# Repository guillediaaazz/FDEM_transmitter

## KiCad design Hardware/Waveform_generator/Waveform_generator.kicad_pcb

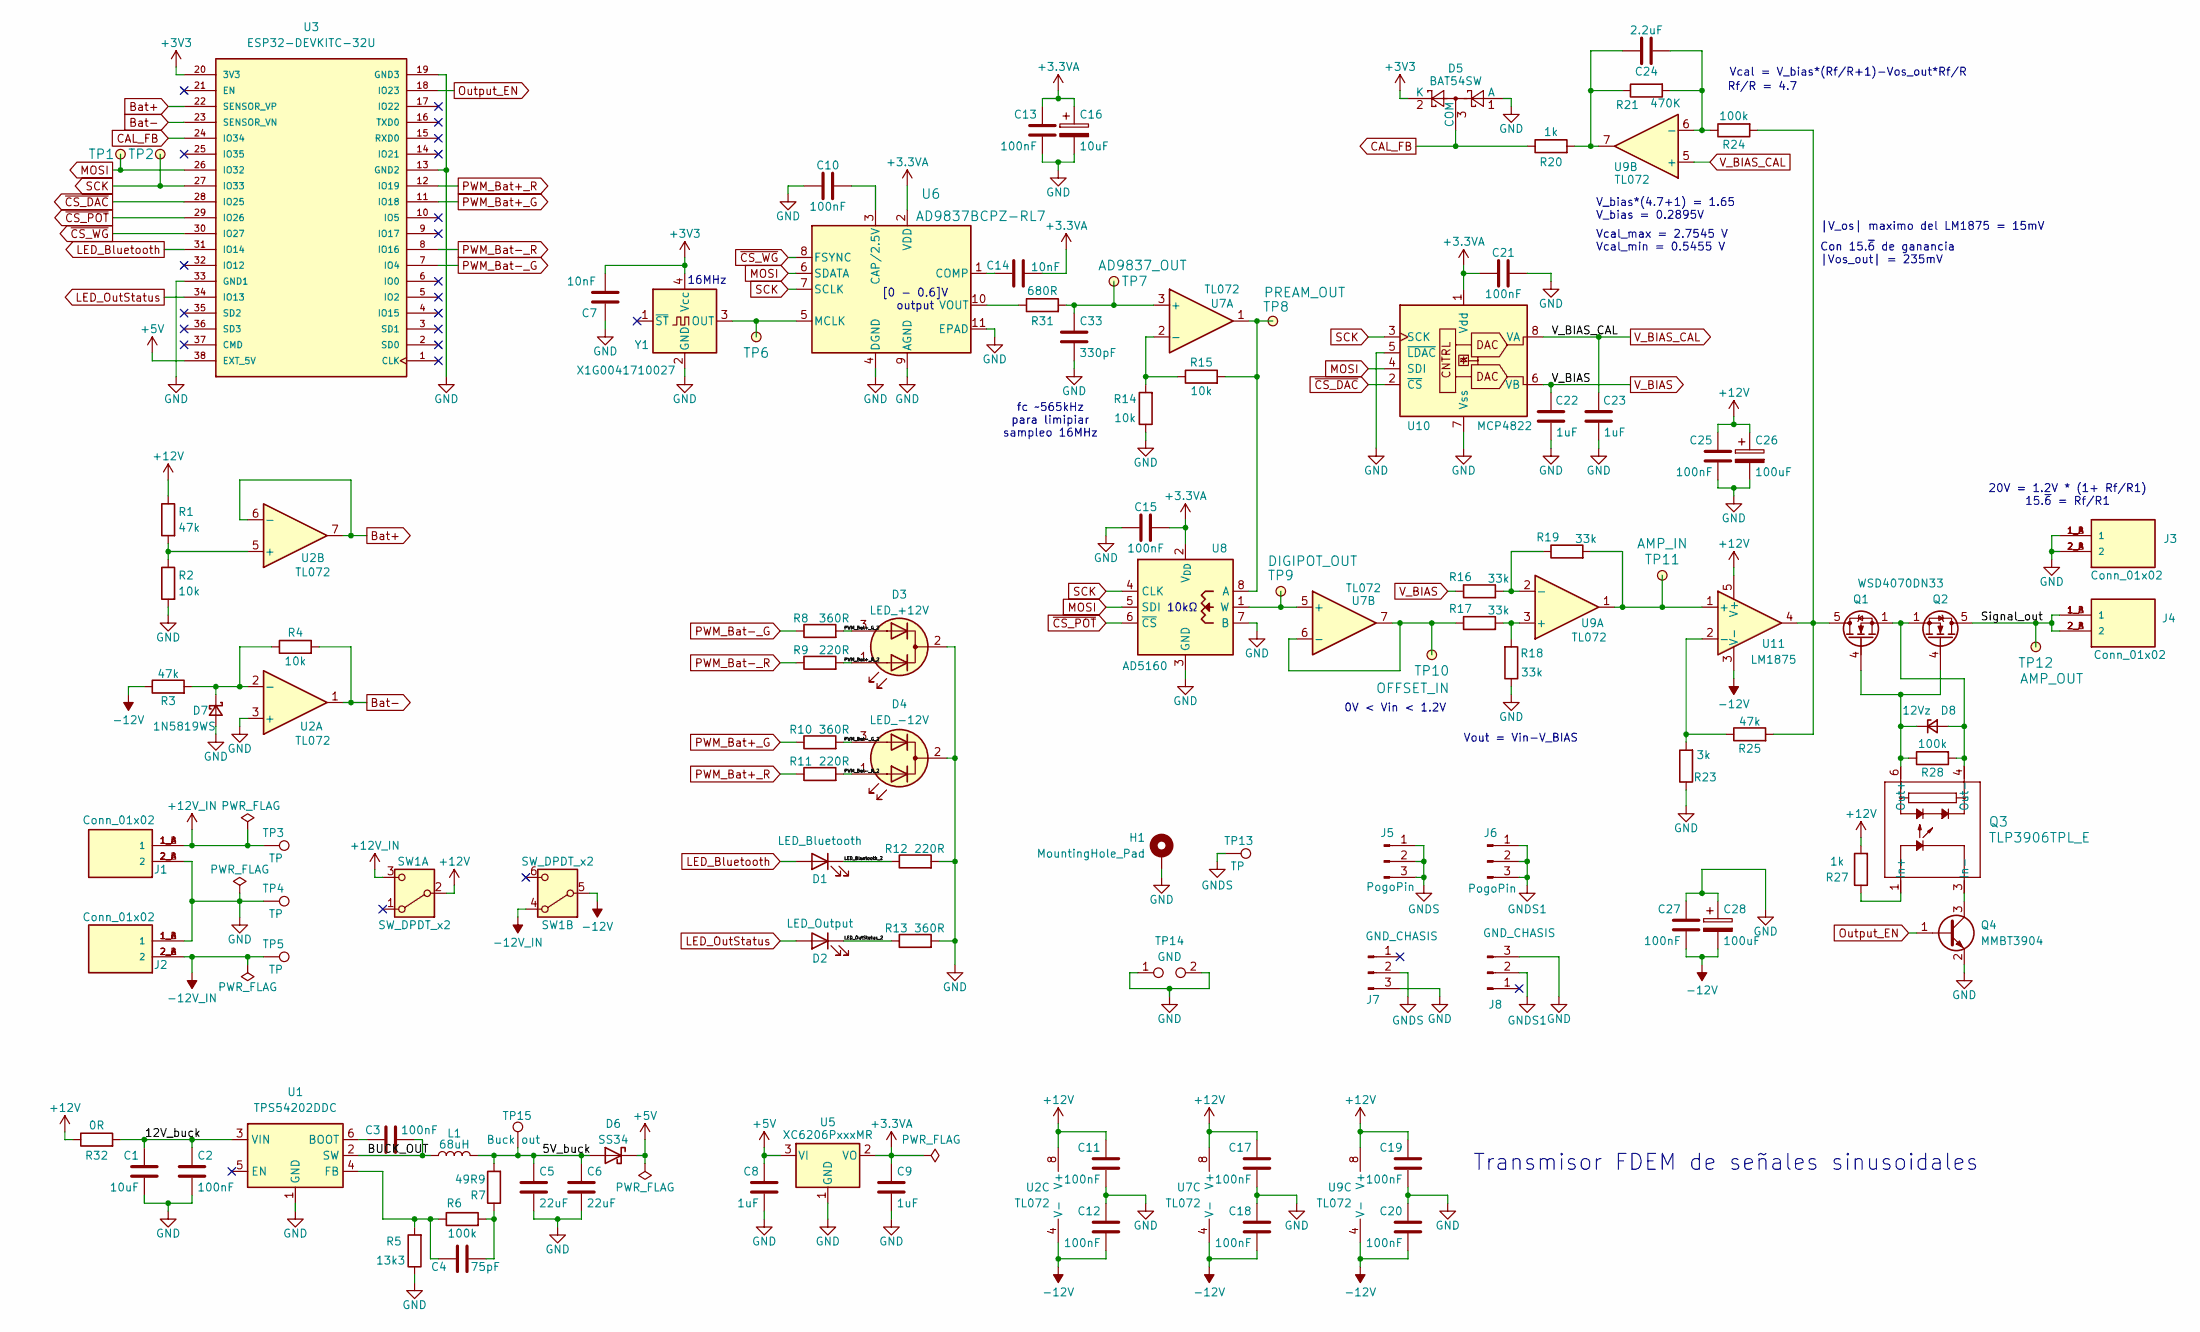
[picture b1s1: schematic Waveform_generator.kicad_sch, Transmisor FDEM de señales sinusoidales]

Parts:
C1: 10uF; C_0805_2012Metric_Pad1.18x1.45mm_HandSolder; LCSC C15850
C2, C3, C10, C11, C12, C13, C15, C17, C18, C19, C20, C21, C25, C27: 100nF; C_0603_1608Metric_Pad1.08x0.95mm_HandSolder; LCSC C14663
C4: 75pF; C_0402_1005Metric_Pad0.74x0.62mm_HandSolder; LCSC C107010
C5, C6: 22uF; C_0603_1608Metric_Pad1.08x0.95mm_HandSolder; LCSC C59461
C7, C14: 10nF; C_0402_1005Metric_Pad0.74x0.62mm_HandSolder; LCSC C15195
C8, C9: 1uF; C_0603_1608Metric_Pad1.08x0.95mm_HandSolder; LCSC C15849
C16: 10uF; CP_EIA-3216-18_Kemet-A_HandSolder; LCSC C7171
C22, C23: 1uF; C_0805_2012Metric_Pad1.18x1.45mm_HandSolder; LCSC C1712
C24: 2.2uF; C_0603_1608Metric_Pad1.08x0.95mm_HandSolder; LCSC C23630
C26, C28: 100uF; CP_Radial_D5.0mm_P2.00mm
C33: 330pF; C_0603_1608Metric_Pad1.08x0.95mm_HandSolder; LCSC C1664
D1: LED_Bluetooth; LED_D3.0mm_Horizontal_O1.27mm_Z2.0mm
D2: LED_Output; LED_D3.0mm_Horizontal_O1.27mm_Z2.0mm
D3: LED_+12V; LED_D3.0mm-3
D4: LED_-12V; LED_D3.0mm-3
D5: BAT54SW; SOT-323_SC-70; LCSC C22466373
D6: SS34; D_SMA; LCSC C8678
D7: 1N5819WS; D_SOD-323_HandSoldering; LCSC C191023
D8: 12Vz; D_SOD-323; LCSC C19077447
H1: MountingHole_Pad; MountingHole_3.2mm_M3_Pad_TopBottom
J1, J2, J3, J4: Conn_01x02; KF142R_2p
J5, J6: PogoPin; Pogo pin 1x3 2.54mm male horizontal
J7: GND_CHASIS; PinHeader_1x03_P2.54mm_Vertical
J8: GND_CHASIS; PinHeader_1x03_P2.54mm_Horizontal
L1: 68uH; L_Sunlord_SWPA6045S; LCSC C53663
Q1, Q2: WSD4070DN33; VSON-8_3.3x3.3mm_P0.65mm_NexFET; LCSC C719095
Q3: TLP3906TPL_E; 4pin SO6_TOS; LCSC C146278
Q4: MMBT3904; SOT-23; LCSC C20526
R1, R3, R25: 47k; R_0603_1608Metric_Pad0.98x0.95mm_HandSolder; LCSC C25819
R2, R4, R14, R15: 10k; R_0805_2012Metric_Pad1.20x1.40mm_HandSolder; LCSC C17414
R5: 13k3; R_0603_1608Metric_Pad0.98x0.95mm_HandSolder; LCSC C25952
R6, R24, R28: 100k; R_0603_1608Metric_Pad0.98x0.95mm_HandSolder; LCSC C25803
R7: 49R9; R_0805_2012Metric_Pad1.20x1.40mm_HandSolder; LCSC C17720
R8, R10, R13: 360R; R_0603_1608Metric_Pad0.98x0.95mm_HandSolder; LCSC C25194
R9, R11, R12: 220R; R_0805_2012Metric_Pad1.20x1.40mm_HandSolder; LCSC C17557
R16, R17, R18, R19: 33k; R_0603_1608Metric_Pad0.98x0.95mm_HandSolder; LCSC C4216
R20, R27: 1k; R_0603_1608Metric_Pad0.98x0.95mm_HandSolder; LCSC C21190
R21: 470K; R_0603_1608Metric_Pad0.98x0.95mm_HandSolder; LCSC C23178
R23: 3k; R_0603_1608Metric_Pad0.98x0.95mm_HandSolder; LCSC C4211
R31: 680R; R_0805_2012Metric_Pad1.20x1.40mm_HandSolder; LCSC C17798
R32: 0R; R_1206_3216Metric_Pad1.30x1.75mm_HandSolder; LCSC C17888
SW1: SW_DPDT_x2; SPDT_6P_MTS-2XX_C4_horizontal
TP1, TP2, TP6: Test Point; TestPoint_THTPad_D2.0mm_Drill1.0mm; Part Number HARWIN_S1751-46
TP3, TP4, TP5, TP13: TP; TestPoint_THTPad_D2.0mm_Drill1.0mm
TP7: AD9837_OUT; TestPoint_THTPad_D2.0mm_Drill1.0mm; Part Number HARWIN_S1751-46
TP8: PREAM_OUT; TestPoint_THTPad_D2.0mm_Drill1.0mm; Part Number HARWIN_S1751-46
TP9: DIGIPOT_OUT; TestPoint_THTPad_D2.0mm_Drill1.0mm; Part Number HARWIN_S1751-46
TP10: OFFSET_IN; TestPoint_THTPad_D2.0mm_Drill1.0mm; Part Number HARWIN_S1751-46
TP11: AMP_IN; TestPoint_THTPad_D2.0mm_Drill1.0mm; Part Number HARWIN_S1751-46
TP12: AMP_OUT; TestPoint_THTPad_D2.0mm_Drill1.0mm; Part Number HARWIN_S1751-46
TP14: GND; PinHeader_1x02_P2.54mm_Vertical
TP15: Buck out; TestPoint_THTPad_D2.0mm_Drill1.0mm
U1: TPS54202DDC; SOT-23-6; LCSC C191884
U2, U7, U9: TL072; SOIC-8_3.9x4.9mm_P1.27mm; LCSC C6961
U3: ESP32-DEVKITC-32U; ESP32_38pin; PARTREV V4
U5: XC6206PxxxMR; SOT-23-3; LCSC C5446
U6: AD9837BCPZ-RL7; 10-Lead LFCSP_WD (CP-10-9); LCSC C138562
U8: AD5160; SOT-23-8; LCSC C40097
U10: MCP4822; SOIC-8_3.9x4.9mm_P1.27mm; LCSC C16040
U11: LM1875; TO-220-5_P3.4x3.7mm_StaggerOdd_Lead3.8mm_Vertical
Y1: X1G0041710027; Oscillator_SMD_SeikoEpson_SG210-4Pin_2.5x2.0mm; LCSC C255993

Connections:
+3.3VA: C9.1, C13.1, C14.2, C15.2, C16.1, C21.1, U5.2 (VO), U6.2 (VDD), U8.2 (V_{DD}), U10.1 (Vdd)
+3V3: C7.2, D5.2 (K), U3.20 (3V3), Y1.4 (Vcc)
+5V: C8.1, D6.1 (K), U3.38 (EXT_5V), U5.3 (VI)
+12V: C11.1, C17.1, C19.1, C25.1, C26.1, R1.1, R27.2, R32.1, SW1.2 (B), U2.8 (V+), U7.8 (V+), U9.8 (V+), U11.5 (V+); also elsewhere on the board
+12V_IN: J1.1_A (1), J1.1_B (1), SW1.3 (C), TP3.1 (1_1)
-12V: C12.2, C18.2, C20.2, C27.2, C28.2, R3.1, SW1.5 (B), U2.4 (V-), U7.4 (V-), U9.4 (V-), U11.3 (V-)
-12V_IN: J2.2_A (2), J2.2_B (2), SW1.4 (A), TP5.1 (1_1)
/5V_buck: C5.1, C6.1, D6.2 (A), L1.2, R7.2, TP15.1 (1_1); also elsewhere on the board
/12V_buck: C1.1, C2.1, R32.2, U1.3 (VIN)
/BUCK_OUT: C3.1, L1.1, U1.2 (SW)
/LED_Bluetooth_2: D1.1 (K), R12.1
/LED_OutStatus_2: D2.1 (K), R13.1
/PWM_Bat+_G_2: D3.3 (A2), R8.2
/PWM_Bat+_R_2: D3.1 (A1), R9.2
/PWM_Bat-_G_2: D4.3 (A2), R10.2
/PWM_Bat-_R_2: D4.1 (A1), R11.2
/Signal_out: J4.1_A (1), J4.1_B (1), J4.2_A (2), J4.2_B (2), Q2.5 (D), TP12.1 (1_1)
Bat+: U2.6 (-), U2.7, U3.22 (SENSOR_VP)
Bat-: R4.2, U2.1, U3.23 (SENSOR_VN)
CAL_FB: D5.3 (COM), R20.1, U3.24 (IO34)
GND: C1.2, C2.2, C5.2, C6.2, C7.1, C8.2, C9.2, C10.1, C11.2, C12.1, C13.2, C15.1, C16.2, C17.2, C18.1, C19.2, C20.1, C21.2, C22.1, C23.1, C25.2, C26.2, C27.1, C28.1, C33.2, D3.2 (K), D4.2 (K), D5.1 (A), D7.2 (A), H1.1 (1_1), J1.2_A (2), J1.2_B (2), J2.1_A (1), J2.1_B (1), J3.1_A (1), J3.1_B (1), J3.2_A (2), J3.2_B (2), J7.3, J8.3, Q4.2 (E), R2.2, R5.1, R12.2, R13.2, R14.1, R18.1, R23.1, TP4.1 (1_1), TP14.1, TP14.2, U1.1 (GND), U2.3 (+), U3.13 (GND2), U3.19 (GND3), U3.33 (GND1), U5.1 (GND), U6.4 (DGND), U6.9 (AGND), U6.11 (EPAD), U8.3 (GND), U8.7 (B), U10.5 (~LDAC), U10.7 (Vss), Y1.2 (GND); also elsewhere on the board
GNDS: J5.1, J5.2, J5.3, J7.2, TP13.1 (1_1)
GNDS1: J6.1, J6.2, J6.3, J8.2
LED_Bluetooth: D1.2 (A), U3.31 (IO14)
LED_OutStatus: D2.2 (A), U3.34 (IO13)
MOSI: TP1.1 (1_1), U3.26 (IO32), U6.6 (SDATA), U8.5 (SDI), U10.4 (SDI)
unnamed: C4.2, R6.2, R7.1
unnamed: C24.1, R20.2, R21.1, U9.7
unnamed: D7.1 (K), R3.2, R4.1, U2.2 (-)
unnamed: D8.1 (K), Q1.4 (G), Q2.4 (G), Q3.6 (Out+), R28.1
unnamed: D8.2 (A), Q1.1 (S), Q1.2 (S), Q1.3 (S), Q2.1 (S), Q2.2 (S), Q2.3 (S), Q3.4 (Out-), R28.2
unnamed 31: Q1.5 (D), R24.2, R25.2, U11.4; also elsewhere on the board
unnamed: Q3.1 (In+), R27.1
unnamed: Q3.3 (In-), Q4.3 (C)
unnamed: C3.2, U1.6 (BOOT)
unnamed: C4.1, R5.2, R6.1, U1.4 (FB)
unnamed: R1.2, R2.1, U2.5 (+)
unnamed: C10.2, U6.3 (CAP/2.5V)
unnamed: C14.1, U6.1 (COMP)
unnamed: TP6.1 (1_1), U6.5 (MCLK), Y1.3 (OUT)
unnamed: R31.1, U6.10 (VOUT)
unnamed: C33.1, R31.2, TP7.1 (1_1), U7.3 (+)
unnamed: R14.2, R15.1, U7.2 (-)
unnamed: TP9.1 (1_1), U7.5 (+), U8.1 (W)
unnamed: R17.1, TP10.1 (1_1), U7.6 (-), U7.7
unnamed: R15.2, TP8.1 (1_1), U7.1, U8.8 (A)
unnamed: R17.2, R18.2, U9.3 (+)
unnamed: R16.2, R19.1, U9.2 (-)
unnamed: C24.2, R21.2, R24.1, U9.6 (-)
unnamed: R19.2, TP11.1 (1_1), U9.1, U11.1 (+)
unnamed 50: R23.2, R25.1, U11.2 (-); also elsewhere on the board
Output_EN: Q4.1 (B), U3.18 (IO23)
PWM_Bat+_G: R10.1, U3.11 (IO18)
PWM_Bat+_R: R11.1, U3.12 (IO19)
PWM_Bat-_G: R8.1, U3.7 (IO4)
PWM_Bat-_R: R9.1, U3.8 (IO16)
SCK: TP2.1 (1_1), U3.27 (IO33), U6.7 (SCLK), U8.4 (CLK), U10.3 (SCK)
V_BIAS: C22.2, R16.1, U10.6 (VB)
V_BIAS_CAL: C23.2, U9.5 (+), U10.8 (VA)
~CS_DAC: U3.28 (IO25), U10.2 (~CS)
~CS_POT: U3.29 (IO26), U8.6 (~CS)
~CS_WG: U3.30 (IO27), U6.8 (FSYNC)

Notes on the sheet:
0V < Vin < 1.2V
Vcal = V_bias*(Rf/R+1)-Vos_out*Rf/R
|V_os| maximo del LM1875 = 15mV
10kΩ
Transmisor FDEM de señales sinusoidales
Rf/R = 4.7
Vout = Vin-V_BIAS
[0 - 0.6]V output
V_bias*(4.7+1) = 1.65 V_bias = 0.2895V
Con 15.~{6} de ganancia |Vos_out| = 235mV
20V = 1.2V * (1+ Rf/R1) 15.~{6} = Rf/R1
16MHz
fc ~565kHz para limipiar sampleo 16MHz
Vcal_max = 2.7545 V Vcal_min = 0.5455 V

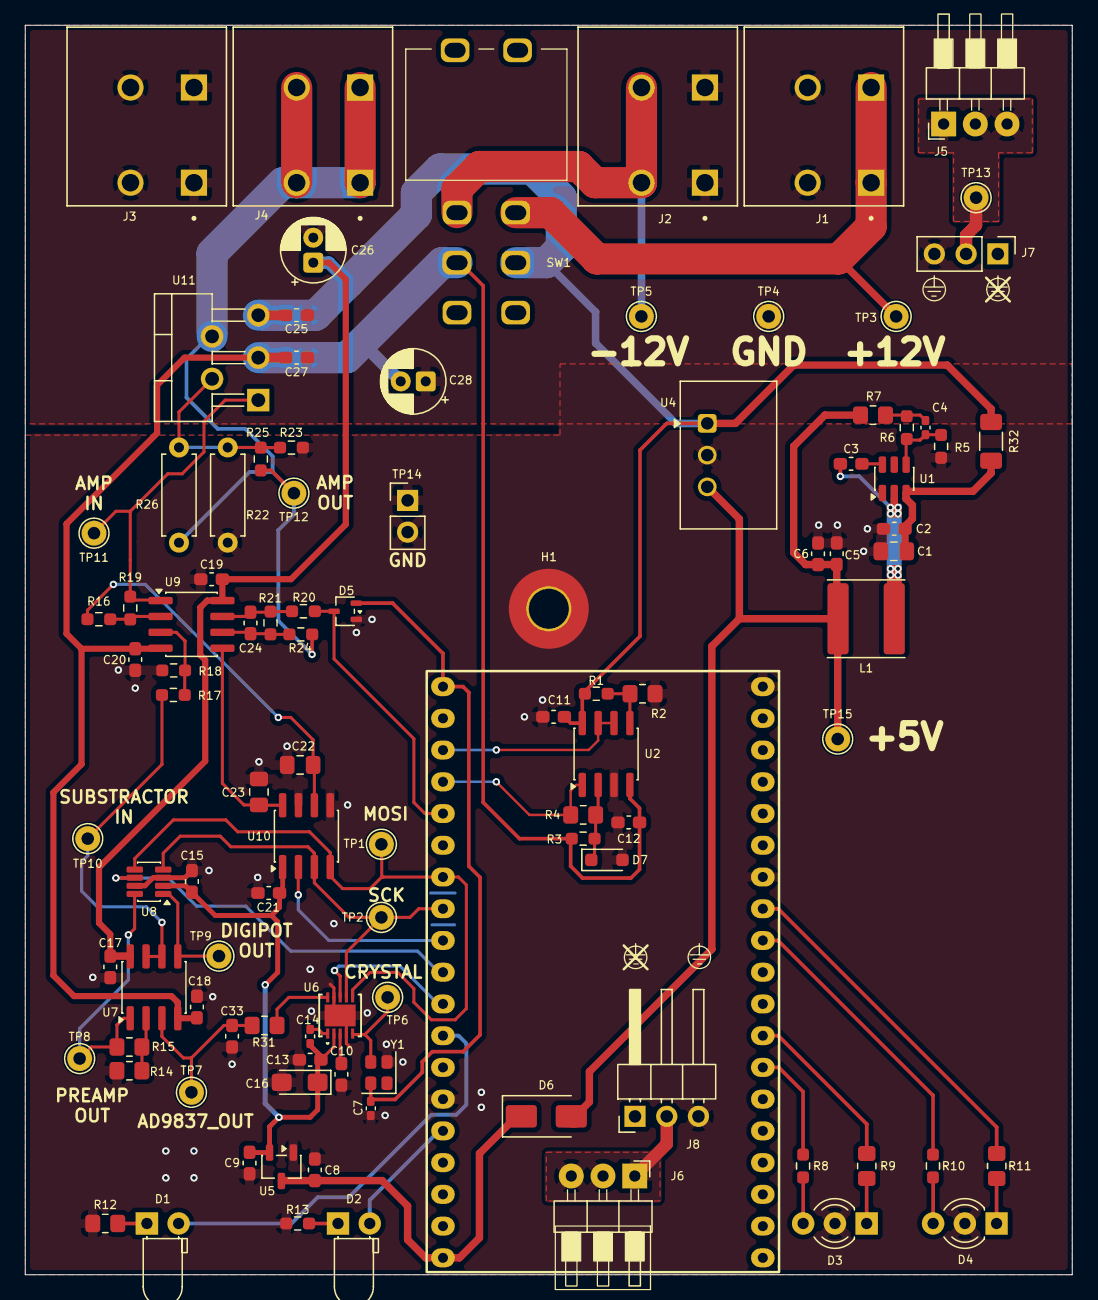
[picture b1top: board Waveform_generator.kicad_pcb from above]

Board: 2 copper layers, 83.8 x 100.0 mm, 102 parts (0 on the bottom side), 57 nets.

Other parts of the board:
R22: 3k; R_Axial_DIN0207_L6.3mm_D2.5mm_P7.62mm_Horizontal
R26: 47k; R_Axial_DIN0207_L6.3mm_D2.5mm_P7.62mm_Horizontal
U4: TSR1-2450E; Converter_DCDC_TRACO_TSR1-xxxxE_THT

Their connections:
+12V: U4.1 (Vin); also elsewhere on the board
/5V_buck: U4.3 (Vout); also elsewhere on the board
GND: R22.1, U4.2 (GND); also elsewhere on the board
unnamed 31: R26.2; also elsewhere on the board
unnamed 50: R22.2, R26.1; also elsewhere on the board

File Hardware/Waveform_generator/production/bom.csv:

Designator,Footprint,Quantity,Value,LCSC Part #
C1,0805,1,10uF,C15850
"C10, C11, C12, C13, C15, C17, C18, C19, C2, C20, C21, C25, C27, C3",0603,14,100nF,C14663
"C14, C7",0402,2,10nF,C15195
C16,CP_EIA-3216-18_Kemet-A_HandSolder,1,10uF,C7171
"C22, C23",0805,2,1uF,C1712
C24,0603,1,2.2uF,C23630
C33,0603,1,330pF,C1664
C4,0402,1,75pF,C107010
"C5, C6",0603,2,22uF,C59461
"C8, C9",0603,2,1uF,C15849
D5,SOT-323_SC-70,1,BAT54SW,C22466373
D6,D_SMA,1,SS34,C8678
"J5, J6",Pogo pin 1x3 2.54mm male horizontal,2,PogoPin,
J7,PinHeader_1x03_P2.54mm_Vertical,1,GND_CHASIS,
J8,PinHeader_1x03_P2.54mm_Horizontal,1,GND_CHASIS,
L1,L_Sunlord_SWPA6045S,1,68uH,C53663
"R1, R25, R3",0603,3,47k,C25819
"R10, R13, R8",0603,3,360R,C25194
"R11, R12, R9",0805,3,220R,C17557
"R14, R15, R2, R4",0805,4,10k,C17414
"R16, R17, R18, R19",0603,4,33k,C4216
R20,0603,1,1k,C21190
R21,0603,1,470K,C23178
R23,0603,1,3k,C4211
"R24, R6",0603,2,100k,C25803
R31,0805,1,680R,C17798
R32,1206,1,0R,C17888
R5,0603,1,13k3,C25952
R7,0805,1,49R9,C17720
TP14,PinHeader_1x02_P2.54mm_Vertical,1,GND,
U1,SOT-23-6,1,TPS54202DDC,C191884
U10,SOIC-8_3.9x4.9mm_P1.27mm,1,MCP4822,C16040
"U2, U7, U9",SOIC-8_3.9x4.9mm_P1.27mm,3,TL072,C6961
U5,SOT-23-3,1,XC6206PxxxMR,C5446
U6,10-Lead LFCSP_WD (CP-10-9),1,AD9837BCPZ-RL7,C138562
U8,SOT-23-8,1,AD5160,C40097
Y1,Oscillator_SMD_SeikoEpson_SG210-4Pin_2.5x2.0mm,1,X1G0041710027,C255993

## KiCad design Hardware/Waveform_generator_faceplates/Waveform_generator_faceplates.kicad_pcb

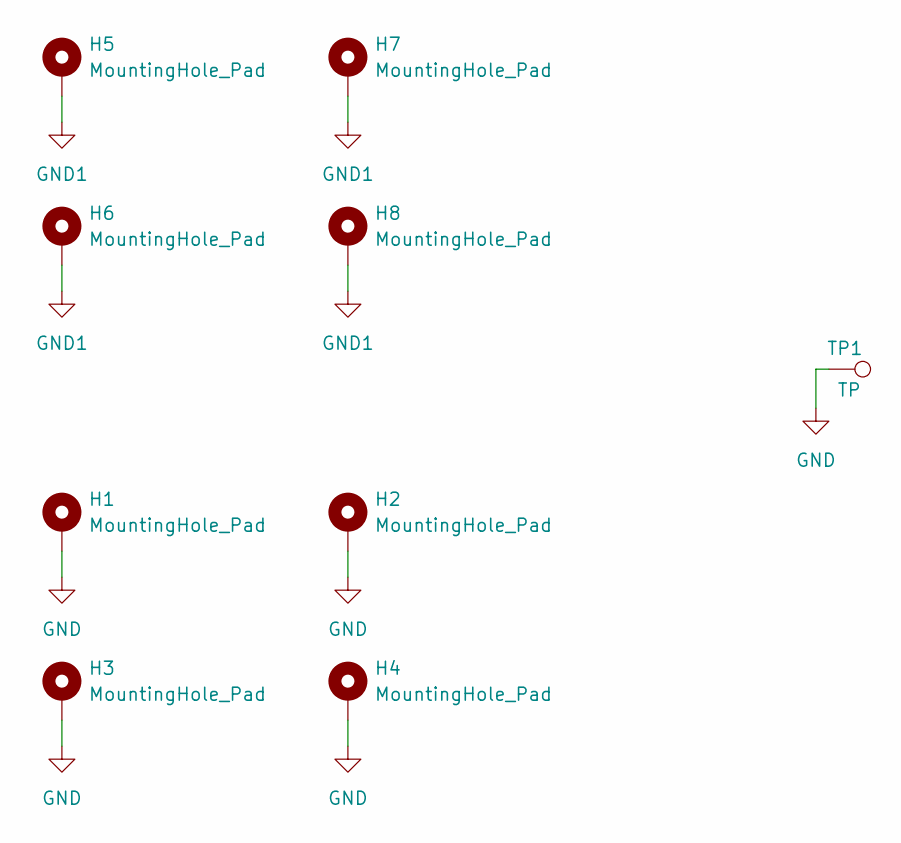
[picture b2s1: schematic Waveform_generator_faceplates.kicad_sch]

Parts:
H1, H2, H3, H4, H5, H6, H7, H8: MountingHole_Pad; M3 hole (3.2mm hole Pad 5mm)
TP1: TP; TestPoint_THTPad_D2.0mm_Drill1.0mm

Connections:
GND: H1.1 (1_1), H2.1 (1_1), H3.1 (1_1), H4.1 (1_1), TP1.1 (1_1)
GND1: H5.1 (1_1), H6.1 (1_1), H7.1 (1_1), H8.1 (1_1)

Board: 2 copper layers, 9 parts (0 on the bottom side), 2 nets, no tracks yet.

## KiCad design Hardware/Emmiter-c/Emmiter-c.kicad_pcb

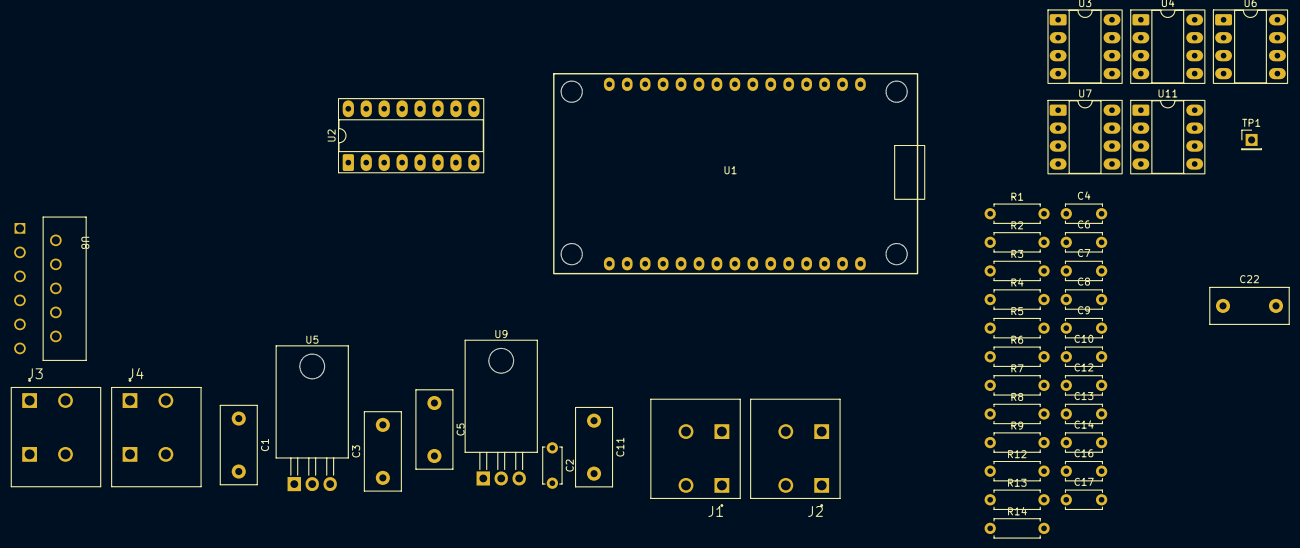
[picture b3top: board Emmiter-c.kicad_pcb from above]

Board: 2 copper layers, 44 parts (0 on the bottom side), 32 nets, no tracks yet.

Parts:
C1, C3, C5, C11: 10uF/T; C_Disc_D11.0mm_W5.0mm_P7.50mm
C2, C4, C6, C7, C8, C9, C10, C12, C13, C14, C16, C17: 100nF; C_Disc_D5.0mm_W2.5mm_P5.00mm
C22: 1uF; C_Disc_D11.0mm_W5.0mm_P7.50mm
J1, J2, J3, J4: Conn_01x02; CUI_TBL004-508-02BE-2BE
R1: 0; R_Axial_DIN0207_L6.3mm_D2.5mm_P7.62mm_Horizontal
R2, R3, R8, R9: 10k; R_Axial_DIN0207_L6.3mm_D2.5mm_P7.62mm_Horizontal
R4: 75k; R_Axial_DIN0207_L6.3mm_D2.5mm_P7.62mm_Horizontal
R5: 4k99; R_Axial_DIN0207_L6.3mm_D2.5mm_P7.62mm_Horizontal
R6, R7: 47k5; R_Axial_DIN0207_L6.3mm_D2.5mm_P7.62mm_Horizontal
R12, R13, R14: R; R_Axial_DIN0207_L6.3mm_D2.5mm_P7.62mm_Horizontal
TP1: Power Ground; PinHeader_1x01_P2.54mm_Vertical
U1: ESP32_30pin
U2: DAC08; DIP-16_W7.62mm_Socket_LongPads
U3, U6, U7: TL072; DIP-8_W7.62mm_Socket_LongPads
U4: MCP4131-xxxx-P; DIP-8_W7.62mm_Socket_LongPads
U5: LM1117T-3.3; TO-220-3_Horizontal_TabDown
U8: OPA549T
U9: LM1117T-5.0; TO-220-3_Horizontal_TabDown
U11: MCP4821; DIP-8_W7.62mm_Socket_LongPads

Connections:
+3V3: C4.1, C7.2, C9.1, C11.1, R9.2, U4.8 (V_{DD}), U5.2 (VO), U11.1 (Vdd)
+5V: C2.2, C3.1, C5.1, U1.1 (VIN), U5.3 (VI), U9.2 (VO)
+12V: C1.1, C6.1, C12.2, C13.1, C16.1, J1.1_A (1), J1.1_B (1), R7.1, U2.13 (V+), U3.4 (V-), U6.8 (V+), U8.10 (V+), U8.11 (V+), U9.3 (VI)
-12V: C8.2, C10.1, C14.2, C17.1, J2.2_A (2), J2.2_B (2), R6.1, U2.3 (V-), U3.8 (V+), U6.4 (V-), U8.5 (V-), U8.7 (V-)
B0: U1.25 (GPIO19), U2.5 (B0)
B1: U1.24 (GPIO18), U2.6 (B1)
B2: U1.23 (GPIO5), U2.7 (B2)
B3: U1.22 (GPIO17), U2.8 (B3)
B4: U1.21 (GPIO16), U2.9 (B4)
B5: U1.20 (GPIO4), U2.10 (B5)
B6: U1.19 (GPIO2), U2.11 (B6)
B7: U1.18 (GPIO15), U2.12 (B7)
Bat+: U6.6 (-), U6.7
Bat-: R3.2, U6.1
GNDA: C1.2, C2.1, C3.2, C4.2, C5.2, C6.2, C7.1, C8.1, C9.2, C10.2, C11.2, C12.1, C13.2, C14.1, C16.2, C17.2, C22.1, J1.2_A (2), J1.2_B (2), J2.1_A (1), J2.1_B (1), J4.2_A (2), J4.2_B (2), R1.2, R5.2, R8.2, R13.2, U2.1 (VLC), U2.4 (I-), U4.4 (V_{SS}), U4.7 (P0B), U5.1 (GND), U6.3 (+), U7.2 (-), U8.6 (REF), U9.1 (GND), U11.7 (Vss)
GNDD: R1.1, U1.2 (GND), U1.17 (GND)
MOSI: U4.3 (SDI/SDO), U11.4 (SDI)
unnamed: J3.1_A (1), J3.1_B (1), J3.2_A (2), J3.2_B (2), R4.2, U8.1, U8.2
unnamed: J4.1_A (1), J4.1_B (1), TP1.1
unnamed: R12.1, U2.2 (I+), U7.3 (+)
unnamed: R14.2, U2.14 (R+)
unnamed: R13.1, U2.15 (R-)
unnamed: R12.2, U4.5 (P0A), U7.1
unnamed: U4.6 (P0W), U7.5 (+)
unnamed: R3.1, R6.2, U6.2 (-)
unnamed: R7.2, R8.1, U6.5 (+)
unnamed: U7.6 (-), U7.7, U8.4 (+)
unnamed: R2.2, R4.1, U8.3 (-)
unnamed: R9.1, U8.9 (E/S)
unnamed: R5.1, U8.8 (ILIM)
unnamed: C22.2, R2.1, U11.8 (Vout)
SCK: U4.2 (SCK), U11.3 (SCK)
